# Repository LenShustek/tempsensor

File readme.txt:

This project consists of four small battery-powered remote wireless temperature sensors, and a single wall-powered receiver for them that replaces the temperature-monitoring thermistors inside wall-mounted thermostats.

My motivation: we have a four-zone Mitsubishi/Honeywell MNET-based HVAC system that was incorrectly designed without temperature monitoring in the zones. We want to avoid breaking walls and ceilings to wire compatible themostats. The Honeywell C7189 wireless indoor remote temperature sensor is not compatible, and we don't like the complicated Mitsubishi MRCH1 wireless remote controller because it's big, ugly, and conflicts with the automation system (Control4) that is supposed to be in control of all the HVAC zones.

This project reinstates the four centrally located wired wall-mounted PAR-21MAA thermostats that were part of the original design, but replaces their temperature-sensing thermistors with resistances generated by "digital potentiometers" controlled by an Arduino-like microprocessor. The wireless remote temperature sensors send periodic wireless packets to the central receiver. The indoor range is several hundred feet.

The first version of the system -- which used an LCD display, the Seeed HC-12 433 Mhz transceiver, and a Teensy LC processor -- was installed in December 2015 and worked well for years. The only annoying issue was that with the best low-power code I could muster, the lifetime of the three AAA batteries in each temperature sensor was only 2-3 months.

That prompted me to make a second version of the temperature sensor that uses an e-Paper display, a HopeRF LoRa 868/915 Mhz transceiver, and a bare ATMega328 processor. The average power utilization is now below 100 uA, which resulted in battery life of well over a year.

Unfortunately Waveshare decided to redesign their e-paper module to be 5V compatible, and the resulting quiescent power drain from the voltage regulator and level shifters destroys the "zero current when sleeping" feature that made me choose e-paper displays in the first place. In addition, some of their older modules are defective and use 100 mA when updating the display instead of the specified 12 mA maximum, which puts battery life back to months, not years. 

That prompted me to make a third version that uses just the raw e-paper display, not the module. It was also an opportunity to exercise my newly-learned skills of designing and fabricating boards with only surface-mount components. The average power utilization is now about 60 uA, so the batteries last almost two years.

Len Shustek
Nov 2015, Jul 2018, Jun 2020

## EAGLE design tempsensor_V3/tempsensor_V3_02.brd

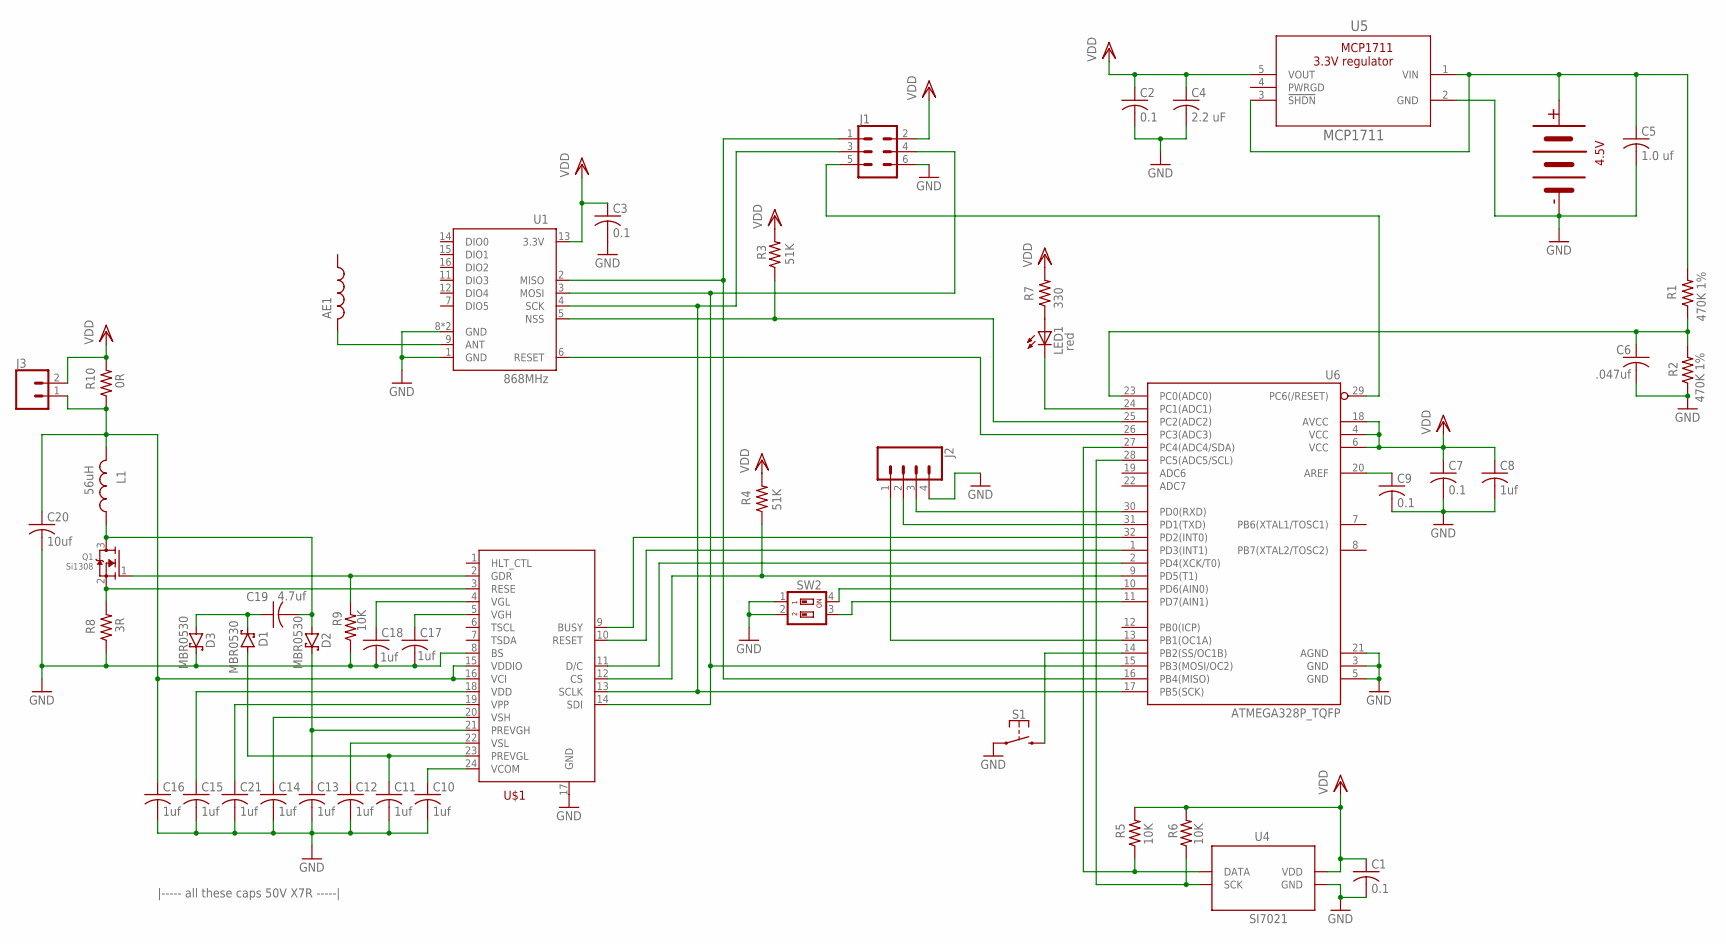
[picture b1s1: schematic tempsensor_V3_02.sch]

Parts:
AE1: ANTENNA-HELICAL; ANTENNA-HELICAL_PULSE_SMD
B1: 3PC-BATTERY-HOLDER; 3AAA-BATTERY-HOLDER
C1, C2, C3, C7, C9: 0.1; C0805
C4: 2.2 uF; C1210
C5: 1.0 uf; C0805
C6: .047uf; C0805
C8, C10, C11, C12, C13, C14, C15, C16, C17, C18, C21: 1uf; C0805
C19: 4.7uf; C1210
C20: 10uf; C1210
D1, D2, D3: MBR0530; SOD123-2
J1: CONN_2X3; 2X3_SMT_RTANGLE_OUTLINE
J2: CONN_04; 1X04
J3: CONN_02; 1X02
L1: 56uH; L1812
LED1: red; LED_PLCC-2
Q1: Si1308; SC70-3-R
R1, R2: 470K 1%; M0805
R3, R4: 51K; M0805
R5, R6, R9: 10K; M0805
R7: 330; M0805
R8: 3R; M0805
R10: 0R; M0805
S1: PUSHBUTTON-SPSTSWITCH_C&K_GULLWING_5MM; SWITCH_C&K_GULLWING_5MM
SW2: SWITCH-2POS-DIP; SMS-002
U1: 868MHz; RFM69HCW-XXXS2
U4: SI7021; DFN-6-3X3-SI7021
U5: MCP1711; SOT-23-5
U6: ATMEGA328P_TQFP; TQFP32-08
U$1: E-PAPER-DISPLAYMOLEX; MOLEX_50511

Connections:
GND: B1.P$1, C1.2, C2.2, C3.2, C4.2, C5.2, C6.2, C7.2, C8.2, C9.2, C10.2, C11.2, C12.2, C13.2, C14.2, C15.2, C16.2, C17.2, C18.2, C20.2, C21.2, D3.P$2 (C), J1.6, J2.4, R2.1, R8.1, R9.1, S1.P$1 (1), S1.P$2 (1), SW2.1, SW2.2, U1.1 (GND), U1.8 (GND), U1.10 (GND), U4.GND, U5.2 (GND), U6.3 (GND), U6.5 (GND), U6.21 (AGND), U$1.8 (BS), U$1.17 (GND)
unnamed: R6.1, U4.SCK, U6.28 (PC5(ADC5/SCL))
unnamed: R5.1, U4.DATA, U6.27 (PC4(ADC4/SDA))
unnamed: J1.4, U1.3 (MOSI), U6.15 (PB3(MOSI/OC2)), U$1.14 (SDI)
unnamed: J1.1, U1.2 (MISO), U6.16 (PB4(MISO))
unnamed: J1.3, U1.4 (SCK), U6.17 (PB5(SCK)), U$1.13 (SCLK)
unnamed: U1.6 (RESET), U6.26 (PC3(ADC3))
unnamed: R3.1, U1.5 (NSS), U6.25 (PC2(ADC2))
unnamed: U6.32 (PD2(INT0)), U$1.9 (BUSY)
unnamed: U6.1 (PD3(INT1)), U$1.10 (RESET)
unnamed: U6.2 (PD4(XCK/T0)), U$1.11 (D/C)
unnamed: R4.1, U6.9 (PD5(T1)), U$1.12 (CS)
unnamed: J2.2, U6.31 (PD1(TXD))
unnamed: LED1.P$2 (C), U6.24 (PC1(ADC1))
unnamed: LED1.P$1 (A), R7.1
unnamed: SW2.4, U6.10 (PD6(AIN0))
unnamed: SW2.3, U6.11 (PD7(AIN1))
unnamed: B1.P$2, C5.1, R1.2, U5.1 (VIN), U5.3 (!SHDN)
unnamed: C9.1, U6.20 (AREF)
unnamed: AE1.P$1, U1.9 (ANT)
unnamed: J1.5, U6.29 (PC6(/RESET))
unnamed: C10.1, U$1.24 (VCOM)
unnamed: C11.1, D1.P$1 (A), U$1.23 (PREVGL)
unnamed: C12.1, U$1.22 (VSL)
unnamed: C13.1, D2.P$2 (C), U$1.21 (PREVGH)
unnamed: C14.1, U$1.20 (VSH)
unnamed: C16.1, C20.1, J3.1, L1.2, R10.1, U$1.15 (VDDIO), U$1.16 (VCI)
unnamed: C6.1, R1.1, R2.2, U6.23 (PC0(ADC0))
unnamed: C15.1, U$1.18 (VDD)
unnamed: C21.1, U$1.19 (VPP)
unnamed: C17.1, U$1.5 (VGH)
unnamed: J2.1, U6.13 (PB1(OC1A))
unnamed: C18.1, U$1.4 (VGL)
unnamed: C19.2, D2.P$1 (A), L1.1, Q1.3 (D)
unnamed: C19.1, D1.P$2 (C), D3.P$1 (A)
unnamed: Q1.1 (G), R9.2, U$1.2 (GDR)
unnamed: Q1.2 (S), R8.2, U$1.3 (RESE)
unnamed: J2.3, U6.30 (PD0(RXD))
unnamed: S1.P$3 (3), S1.P$4 (3), U6.14 (PB2(SS/OC1B))
PWRGD: U5.4 (PWRGD)
VDD: C1.1, C2.1, C3.1, C4.1, C7.1, C8.1, J1.2, J3.2, R3.2, R4.2, R5.2, R6.2, R7.2, R10.2, U1.13 (3.3V), U4.VDD, U5.5 (VOUT), U6.4 (VCC), U6.6 (VCC), U6.18 (AVCC)

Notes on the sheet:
|----- all these caps 50V X7R -----|

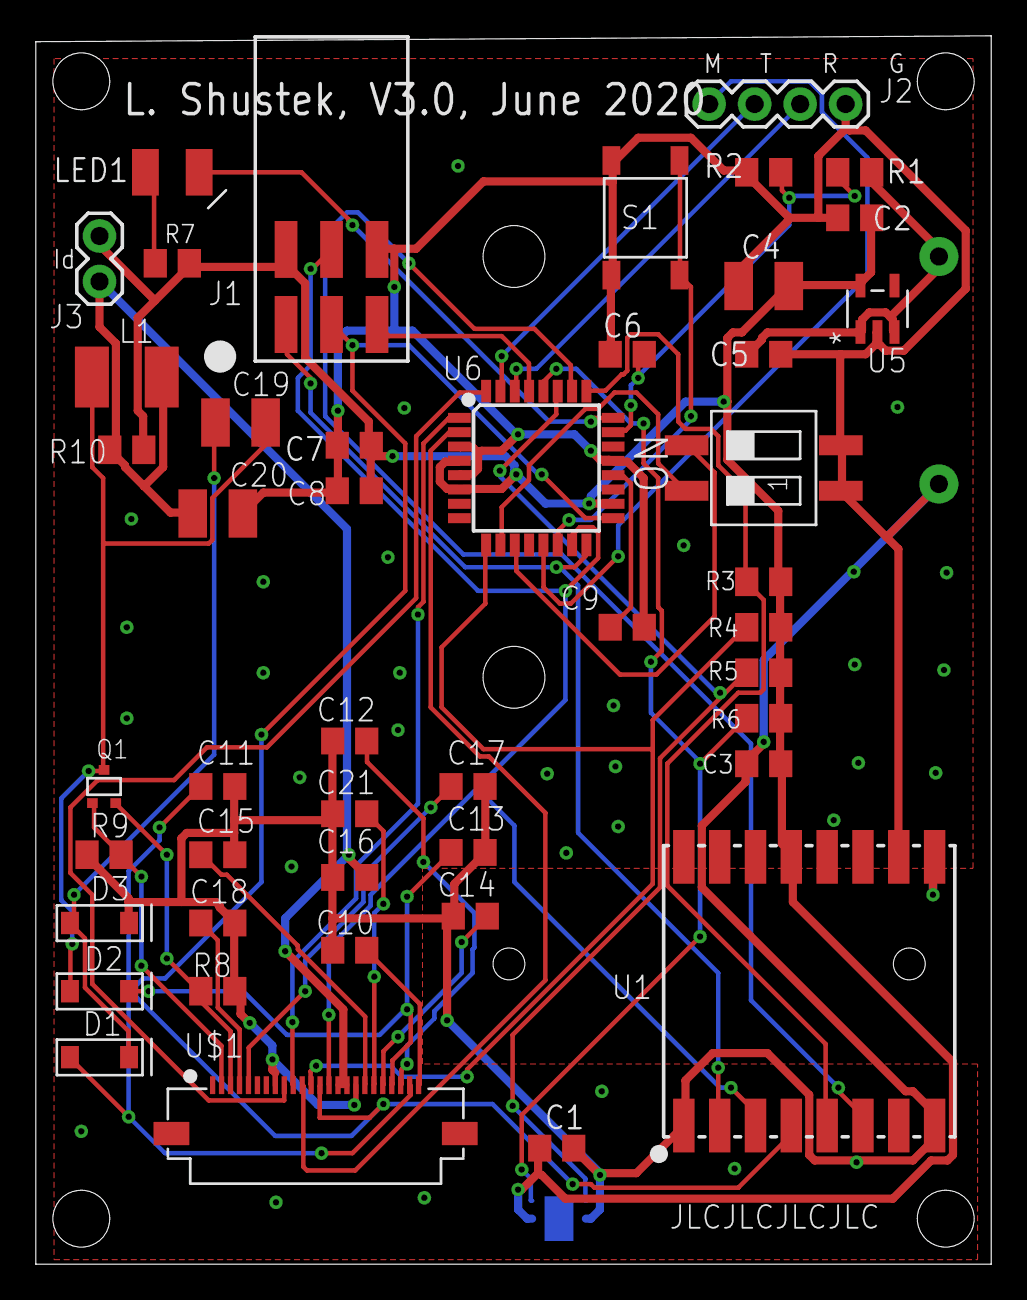
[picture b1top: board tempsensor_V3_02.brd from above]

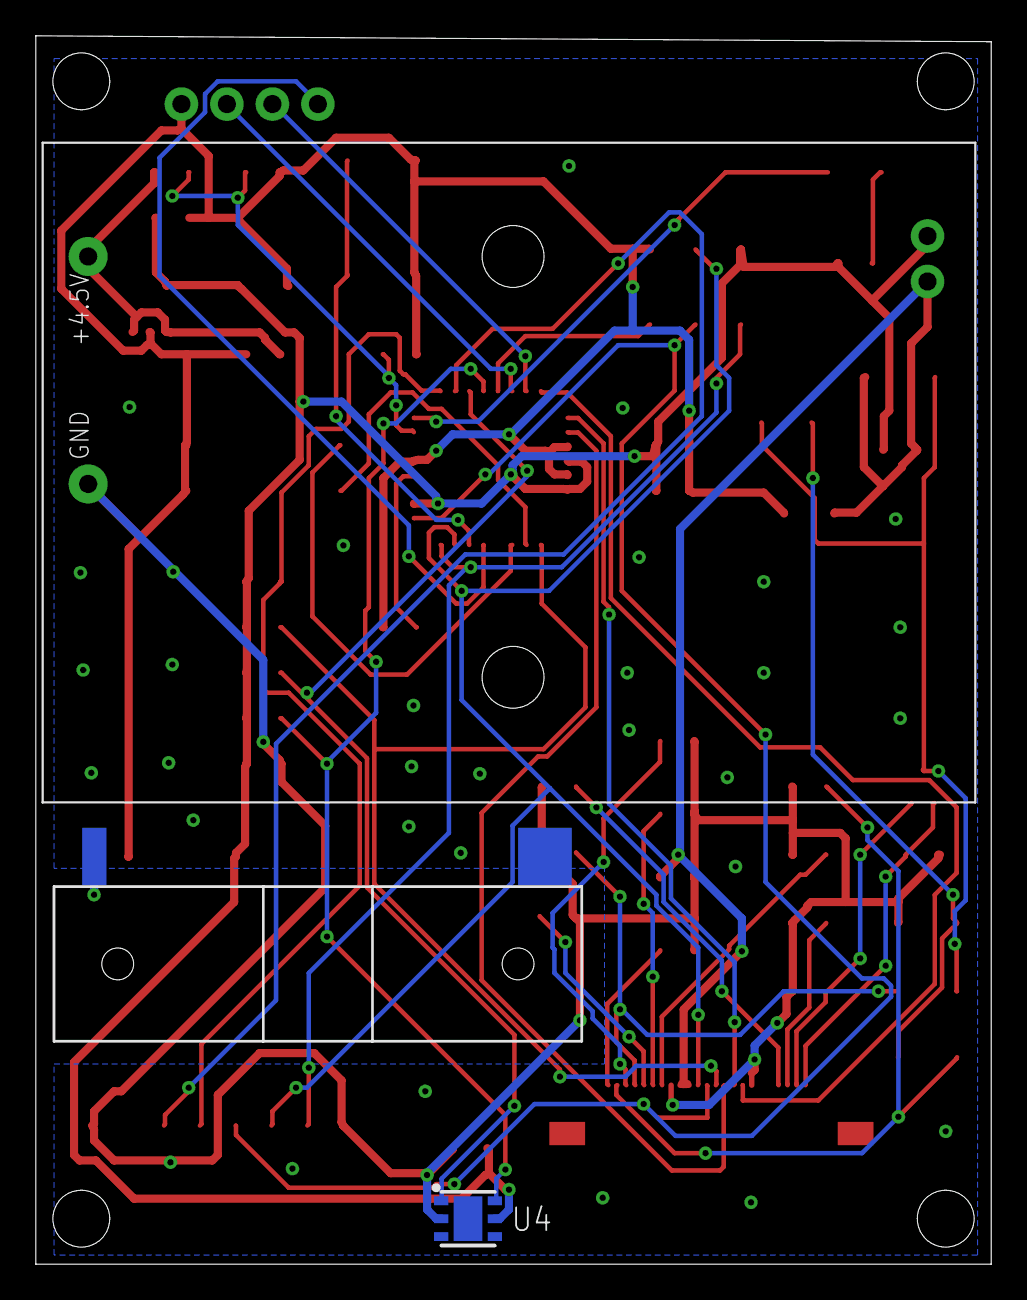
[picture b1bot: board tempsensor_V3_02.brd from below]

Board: 2 copper layers, 53.3 x 68.6 mm, 49 parts (3 on the bottom side), 40 nets.

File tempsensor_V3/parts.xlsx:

|  | Tempsensor V3.0 parts
# per unit | # for all units | have | order | descr | for | ref | manuf | manuf p/n | vendor | vendor p/n | price each
1 | 5 | 4 |  | 4xAAA battery holder |  | B1 | Keystone | 2479 | Mouser | 534-2479 | 1.61
5 | 25 |  | 100 | 0.1 ufd 50V X7R SMD 0805 capacitor |  | C1,C2,C3,C7,C9 | Kemet | C0805C104K5RACTU | Mouser | 80-C0805C104K5R | 5.6000000000000001E-2
1 | 5 |  | 10 | 4.7 ufd 50V X7R SMD 1210 capacitor |  | C19 | Kemet | C1210C475K5RAC | Mouser | 80-C1210C475K5RAC | 0.48399999999999999
1 | 5 | 5 | 10 | 10 ufd 25V X7R SMD 1210 capacitor |  | C20 | Kemet | C1210C106M3RACTU | Mouser | 80-C1210C106M3R | 0.38600000000000001
1 | 5 |  | 10 | 2.2 ufd 50V X7R SMD 1210 capacitor |  | C4 | Kemet | C1210C225K5RACTU | Mouser | 80-C1210C225K5R | 0.44800000000000001
12 | 60 |  | 100 | 1.0 ufd 50V X7R SMD 0805 capacitor |  | C5,C8,C10-18,C21 | Kemet | C0805C105K5RACTU | Mouser | 80-C0805C105K5R | 0.16600000000000001
1 | 5 |  | 100 | .047ufd 50V SMD 0805 capacitor |  | C6 | Kemet | C0805C473K5RACTU | Mouser | 80-C0805C473K5R | 5.6000000000000001E-2
3 | 15 |  | 100 | MBR0530 Schottky diode |  | D1,D2,D3 | ON Semi | MBR0530T1G | Mouser | 863-MBR0530T1G | 8.4000000000000005E-2
1 | 5 |  | 20 | 2x6 SMD pin header 0.1" vertical | programming | J1 | molex | 15-91-0060 | Mouser | 538-15-91-0060 | 0.35499999999999998
1 | 5 |  | 10 | 2x6 SMD pin header 0.1" rt angle | programming | J2 | Samtec | TSM-103-01-S-DH-TR TSM-103-01-L-DH | Mouser Digikey | 200-TSM10301SDHTR SAM9026-ND | 1.48 0.88
1 | 5 | lots |  | 1x3 through hole pin header 0.1" | debugging | J2
1 | 5 | 18 |  | 56 uH inductor SMD 1812 | filter | L1 | Bourns | PM1812-560J-RC | Mouser | 542-PM1812-560J-RC | 0.31
1 | 5 |  | 25 | red LED, SMD PLCC-2, flat top, 2mm high |  | LED1 | OSRAM | LS T67F-T2V2-1-1-Z | Mouser | 720-LST67FT2V211Z | 0.27
1 | 5 |  | 25 | Si1308 N-channel MOSFET |  | Q1 | Vishay | SI1308EDL-T1-GE3 | Mouser Digikey | 78-SI1308EDL-T1-GE3 SI1308EDL-T1-GE3CT-ND | 0.45
2 | 10 | some |  | 470K 1% 1/8W SMD 0805 resistor |  | R1,R2
2 | 10 | some |  | 51K 1% 1/8W SMD 0805 resistor |  | R3,R4
3 | 15 | some |  | 10K 1% 1/8W SMD 0805 resistor |  | R5,R6,R9
1 | 5 | some |  | 330 ohm 1% 1/8W SMD 0805 resistor |  | R7
1 | 5 | some |  | 3 ohm 1% 1/8W SMD 0805 resistor |  | R8
1 | 5 |  | 10 | 2-position SPST slide switch, gull wing SMD | node address | SW2 | CTS | 219-2MSTRF | Mouser | 774-2192MSTRF | 0.623
1 | 5 |  | 10 | FPC connector, 24-pin, SMD, bottom contact |  | U$1 | Molex | 505110-2491 | Mouser | 538-505110-2491 | 0.71399999999999997
1 | 5 |  | 2 | RFM95 RF 868 Mz radio transceiver |  | U1 | Seeed | 109990166 | Seeed Digikey | 109990166 1597-1488-ND | 6.95 7.09
1 | 5 |  | 5 | Si7021-A20 temperature/humidity sensor |  | U4 | Silicon Labs | SI7021-A20-IM1 | Mouser | 634-SI7021-A20-IM1 | 3.53
1 | 5 | 13 |  | MCP1711 3.3V voltage regulator |  | U5 | Microchip | MCP1711T-33I/OT | Mouser | 579-MCP1711T-33I/OT | 0.37
1 | 5 | 2 | 10 | ATMega328P processor, SMD TQFP-44 |  | U6 | Microchip | ATMEGA328P-AUR | Mouser Digikey | 556-ATMEGA328P-AUR ATMEGA328P-AURCT-ND | 1.73
1 | 5 |  | 5 | 1.54" e-paper B/W display |  |  | Crystalfonz Waveshare | CFAP200200A1-0154 1`2955 | Crystalfonz Waveshare |  | 12.64 12.99 | https://www.amazon.com/Waveshare-Resolution-Electronic-Contr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
1 | 5 |  | 5 | 868 Mhz helical antenna |  |  | PulseLarsen Ants | W3136 | Digikey | 1837-1134-2-ND | 1.36
1 | 5 |  | 25 | pushbutton, SPST mom, gullwing SMT |  |  | C&K | PTS525SM15SMTR2 LFS | Digikey | CKN9104CT-ND | 0.32
5 | units to build

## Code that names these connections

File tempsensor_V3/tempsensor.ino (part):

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// pin assignments

// The #define numbers are the Arduino "fake" pin numbers
#define RF_CS_PIN A2      // RF radio chip select, PC2, PDIP pin 25, TQFP pin 25
#define RF_RESET_PIN A3   // RF radio reset, PC2, PDIP pin 26, TQFP pin 26
#define BATTERY_PIN A0    // battery voltage/2, PC0, PDIP pin 23, TQFP pin 23
#define SW1 6             // node address MSB, PD6, PDIP pin 12, TQFP pin 10
#define SW2 7             // node address LSB, PD7, PDIP pin 13, TQFP pin 11
#define LED A1            // LED, active low, PC1, TQFP pin 24
#define DEBUG_SWITCH 10   // pushbutton, active low, PB2, TQFP pin 14
// The pin assignments for the e-paper display are in display.h!

// The following time marker output is a dedicated output pin:
#define TIME_MARKER_PIN 9   // PB1, PDIP pin 15, TQFP pin 13
#define TIME_MARKER_PORT 0x05  // r/w data port B, 0-based address for SBI/CBI instructions
#define TIME_MARKER_BIT 1      // bit number (not mask)
// The following marker users the TxD pin that is already wired to a header, but is incompatible with DEBUG
//#define TIME_MARKER_PIN 1   // PD1, TQFP pin 31
//#define TIME_MARKER_PORT 0x0b  // r/w data port D, 0-based address for SBI/CBI instructions
//#define TIME_MARKER_BIT 1      // bit number (not mask)


// implicit pins used are:
//    MOSI: arduino pin 11, PB3, PDIP pin 17, TQFP pin 15
//    MISO: arduino pin 12, PB4, PDIP pin 18, TQFP pin 16
//    SCK:  arduino pin 13, PB5, PDIP pin 19, TQFP pin 17

byte node_addr;             // 0..3
byte current_temp = 0;      // degrees F
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
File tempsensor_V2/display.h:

//file: display.h

// pin numbers are *Arduino* fake pin numbers
#define DSP_CS_PIN 5  // chip select, PD5, PDIP pin 11, TQFP pin 9
#define DSP_CS_PORT 0x0b    // r/w data port D, 0-based address for SBI/CBI instructions
#define DSP_CS_BIT  5       // bit number
#define DSP_DC_PIN 4   // data/cmd, PD4, PDIP pin 6, TQFP pin 2
#define DSP_DC_PORT 0x0b    // r/w data port D, 0-based address for SBI/CBI instructions
#define DSP_DC_BIT  4       // bit number
#define DSP_RESET_PIN 3  // reset, PD3, PDIP pin 5, TQFP pin 1
#define DSP_BUSY_PIN 2   // busy, PD2, PDIP pin 4, TQFP pin 32


#define EPD_WIDTH   200
#define EPD_HEIGHT  200

#define DSP_MIN_ASCII 32   // space
#define DSP_MAX_ASCII 126  // tilde
#define DSP_NUM_ASCII (DSP_MAX_ASCII-DSP_MIN_ASCII+1)

struct font_t { // generalized description of of a fixed-width font, in flash memory
   byte charw;         // width of each character in pixels; must be a multiple of 8
   byte charh;         // height of each character in pixels; can be arbitrary
   byte charmap[DSP_NUM_ASCII];   // map from ASCII into the character position below; 0xff if absent
   const byte * PROGMEM fontdata;   // ptr to an array in flash memory of charw/8 * charh bytes for each character present in the charmap
} ;
#define XX 0xff     // marker for "no character"

extern const struct font_t font24 PROGMEM;
extern const struct font_t font34 PROGMEM;
extern const struct font_t font67 PROGMEM;

bool dsp_init (void);
void dsp_sleep(void) ;
void dsp_start(bool full_update);
void dsp_clearmem(void);
void dsp_displaymem(bool wait);
bool dsp_busy(void);
void dsp_setmemarea(int x_start, int y_start, int x_end, int y_end);  // set window position in display
void dsp_setmemptr (int x, int y);
void dsp_senddata(byte *ptr, int cnt);
void dsp_writestr_mag(const struct font_t *font, int x, int y, int magnification, char *msg);
void dsp_writestr(const struct font_t *font, int x, int y, char *msg);

//* file.h

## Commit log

2015-12-02 :confetti_ball: Added .gitattributes & .gitignore files
2015-12-02 first version
2015-12-02 photo of receiver box
2015-12-02 photo of remote temperature sensor
2015-12-02 schematic of receiver
2015-12-02 source code for receiver
2015-12-02 source code for remote temp sensor
2015-12-02 schematic of temperature sensor
2015-12-02 PC board layout of temperature sensor
2015-12-24 photo of the receiver installation
2015-12-24 closeup photo of receiver box
2015-12-24 after complete installation
2015-12-24 source code for remote temperature sensor
2015-12-24 after installation
2018-08-31 Version 2: lower power for better battery life
2019-02-04 Update tempsensor.ino
    Fix date update bug
2020-06-26 version 3 of temperature sensor

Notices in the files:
tempsensor_V3/tempsensor.ino:
Copyright (C) 2015,2018,2020 Len Shustek
The MIT License (MIT): Permission is hereby granted, free of charge, to any
parts and their libraries:
SparkFun-Connectors: Licensing: Creative Commons ShareAlike 4.0 International - https://creativecommons.org/licenses/by-sa/4.0
